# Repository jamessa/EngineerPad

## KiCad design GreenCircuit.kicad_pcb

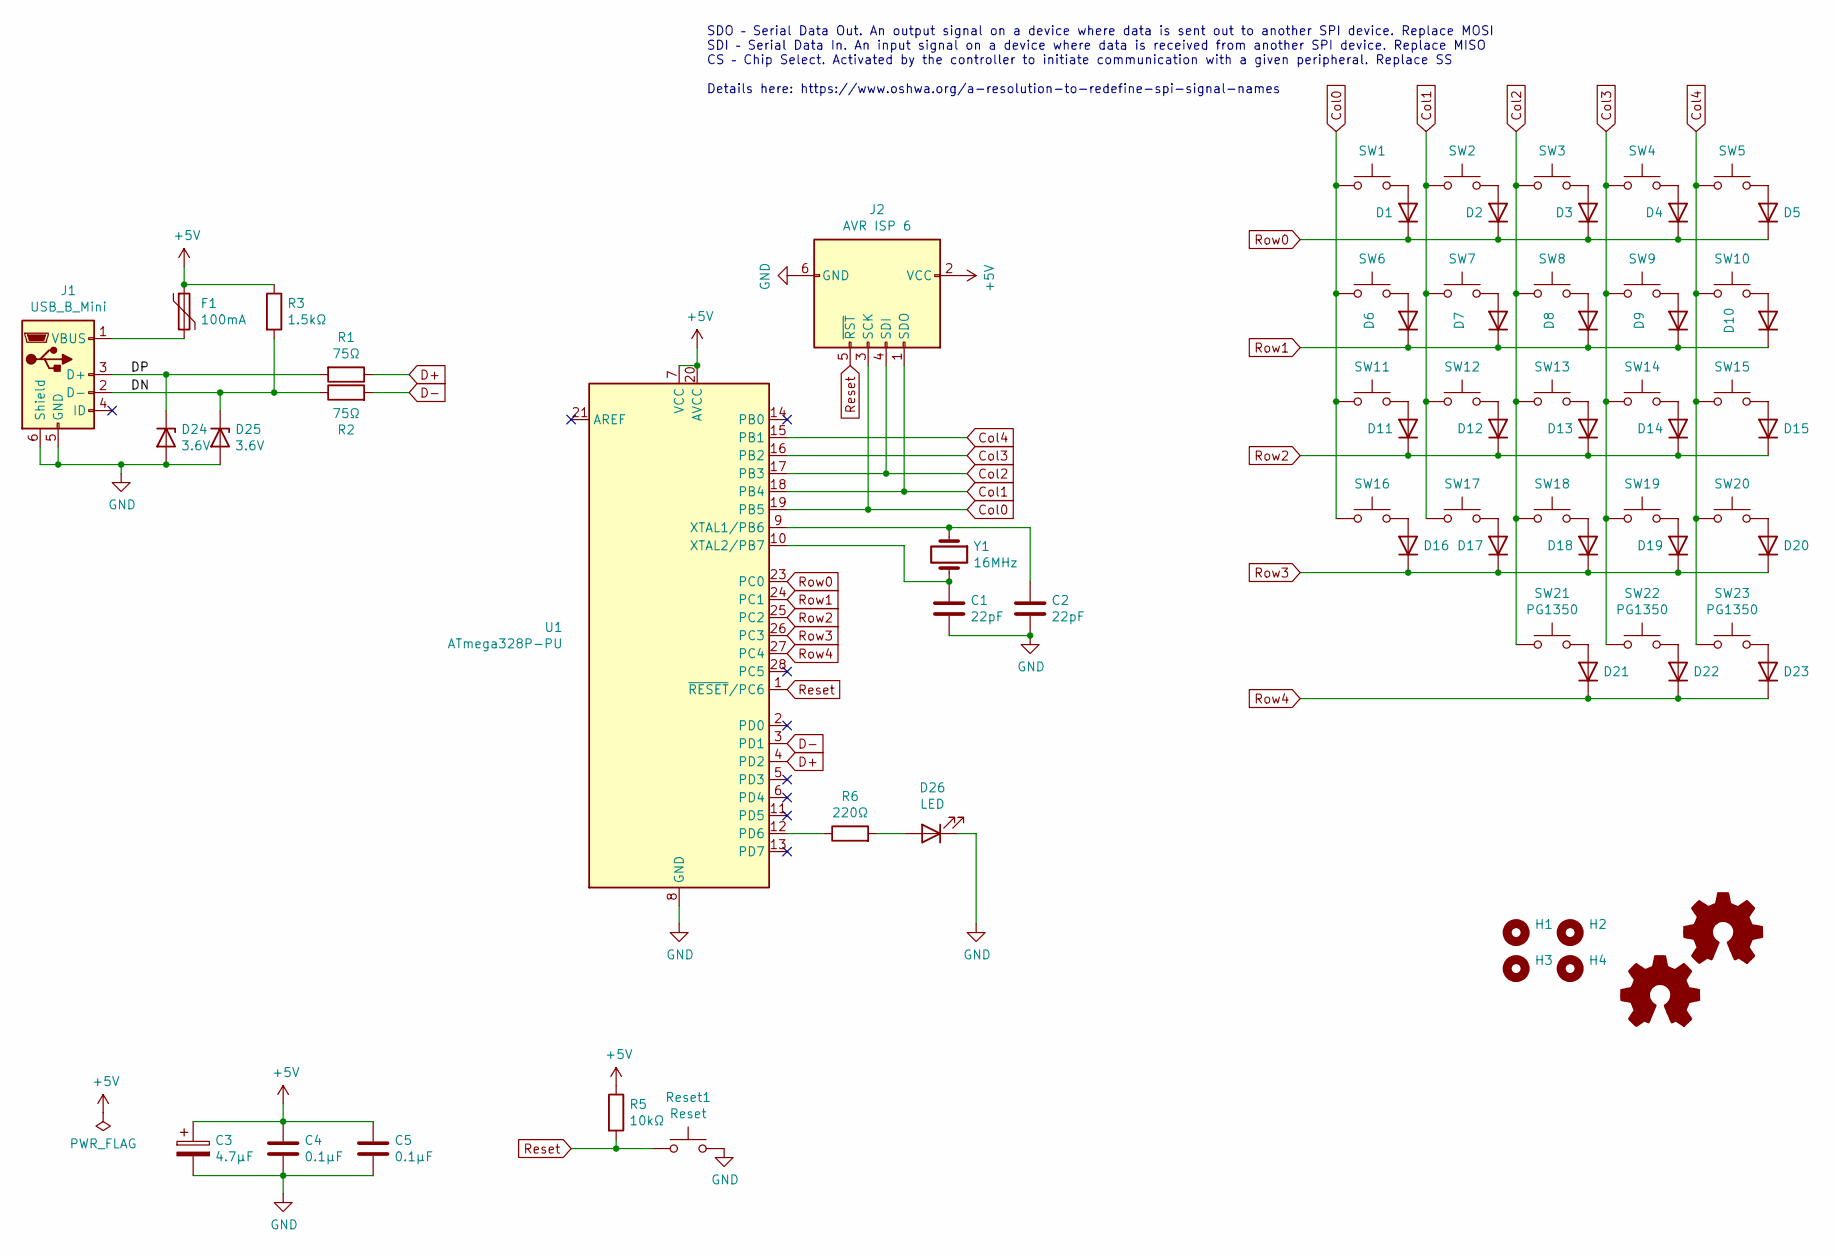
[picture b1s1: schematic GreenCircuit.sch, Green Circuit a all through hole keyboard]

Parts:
C1, C2: 22pF; C_Disc_D3.0mm_W1.6mm_P2.50mm
C3: 4.7μF; CP_Radial_D4.0mm_P1.50mm
C4, C5: 0.1μF; C_Disc_D4.3mm_W1.9mm_P5.00mm
D1, D2, D3, D4, D5, D6, D7, D8, D9, D10, D11, D12, D13, D14, D15, D16, D17, D18, D19, D20, D21, D22, D23: D; Diode_THT
D24, D25: 3.6V; D_DO-35_SOD27_P7.62mm_Horizontal
D26: LED; LED_D3.0mm
F1: 100mA; Fuse_Bourns_MF-RHT050
H1, H2, H3, H4: MountingHole; MountingHole_3.2mm_M3
J1: USB_B_Mini; USB_Mini_B_Female_548190519
J2: AVR ISP 6; AVRISP
R1, R2: 75Ω; R_Axial_DIN0207_L6.3mm_D2.5mm_P7.62mm_Horizontal
R3: 1.5kΩ; R_Axial_DIN0207_L6.3mm_D2.5mm_P7.62mm_Horizontal
R5: 10kΩ; R_Axial_DIN0207_L6.3mm_D2.5mm_P7.62mm_Horizontal
R6: 220Ω; R_Axial_DIN0207_L6.3mm_D2.5mm_P7.62mm_Horizontal
Reset1: Reset; SW_PUSH_6mm
SW1, SW2, SW3, SW4, SW5, SW6, SW7, SW8, SW9, SW10, SW11, SW12, SW13, SW14, SW15, SW16, SW17, SW18, SW19, SW20: SW_Push; SW_Cherry_MX_1.00u_PCB
SW21, SW22, SW23: PG1350; SW_PG1350
U1: ATmega328P-PU; DIP-28_W7.62mm_Socket
Y1: 16MHz; Crystal_HC49-4H_Vertical

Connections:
+5V: C3.1, C4.1, C5.1, F1.1, J2.2 (VCC), R3.1, R5.1, U1.7 (VCC), U1.20 (AVCC)
/DN: D25.1 (K), J1.2 (D-), R2.1, R3.2
/DP: D24.1 (K), J1.3 (D+), R1.2
Col0: J2.3 (SCK), SW1.1, SW6.1, SW11.1, SW16.1, U1.19 (PB5)
Col1: J2.1 (SDO), SW2.1, SW7.1, SW12.1, SW17.1, U1.18 (PB4)
Col2: J2.4 (SDI), SW3.1, SW8.1, SW13.1, SW18.1, SW21.1, U1.17 (PB3)
Col3: SW4.1, SW9.1, SW14.1, SW19.1, SW22.1, U1.16 (PB2)
Col4: SW5.1, SW10.1, SW15.1, SW20.1, SW23.1, U1.15 (PB1)
D+: R1.1, U1.4 (PD2)
D-: R2.2, U1.3 (PD1)
GND: C1.1, C2.1, C3.2, C4.2, C5.2, D24.2 (A), D25.2 (A), D26.1 (K), J1.5 (GND), J1.6 (Shield), J2.6 (GND), Reset1.2, U1.8 (GND), U1.22 (GND)
unnamed: C1.2, U1.10 (XTAL2/PB7), Y1.2
unnamed: C2.2, U1.9 (XTAL1/PB6), Y1.1
unnamed: D1.2 (A), SW1.2
unnamed: D2.2 (A), SW2.2
unnamed: D3.2 (A), SW3.2
unnamed: D4.2 (A), SW4.2
unnamed: D5.2 (A), SW5.2
unnamed: D6.2 (A), SW6.2
unnamed: D7.2 (A), SW7.2
unnamed: D8.2 (A), SW8.2
unnamed: D9.2 (A), SW9.2
unnamed: D10.2 (A), SW10.2
unnamed: D11.2 (A), SW11.2
unnamed: D12.2 (A), SW12.2
unnamed: D13.2 (A), SW13.2
unnamed: D14.2 (A), SW14.2
unnamed: D15.2 (A), SW15.2
unnamed: D16.2 (A), SW16.2
unnamed: D17.2 (A), SW17.2
unnamed: D18.2 (A), SW18.2
unnamed: D19.2 (A), SW19.2
unnamed: D20.2 (A), SW20.2
unnamed: D21.2 (A), SW21.2
unnamed: D22.2 (A), SW22.2
unnamed: D23.2 (A), SW23.2
unnamed: D26.2 (A), R6.2
unnamed: F1.2, J1.1 (VBUS)
unnamed: R6.1, U1.12 (PD6)
Reset: J2.5 (~RST), R5.2, Reset1.1, U1.1 (~RESET~/PC6)
Row0: D1.1 (K), D2.1 (K), D3.1 (K), D4.1 (K), D5.1 (K), U1.23 (PC0)
Row1: D6.1 (K), D7.1 (K), D8.1 (K), D9.1 (K), D10.1 (K), U1.24 (PC1)
Row2: D11.1 (K), D12.1 (K), D13.1 (K), D14.1 (K), D15.1 (K), U1.25 (PC2)
Row3: D16.1 (K), D17.1 (K), D18.1 (K), D19.1 (K), D20.1 (K), U1.26 (PC3)
Row4: D21.1 (K), D22.1 (K), D23.1 (K), U1.27 (PC4)

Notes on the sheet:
SDO – Serial Data Out. An output signal on a device where data is sent out to another SPI device. Replace MOSI SDI – Serial Data In. An input signal on a device where data is received from another SPI device. Replace MISO CS – Chip Select. Activated by the controller to initiate communication with 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

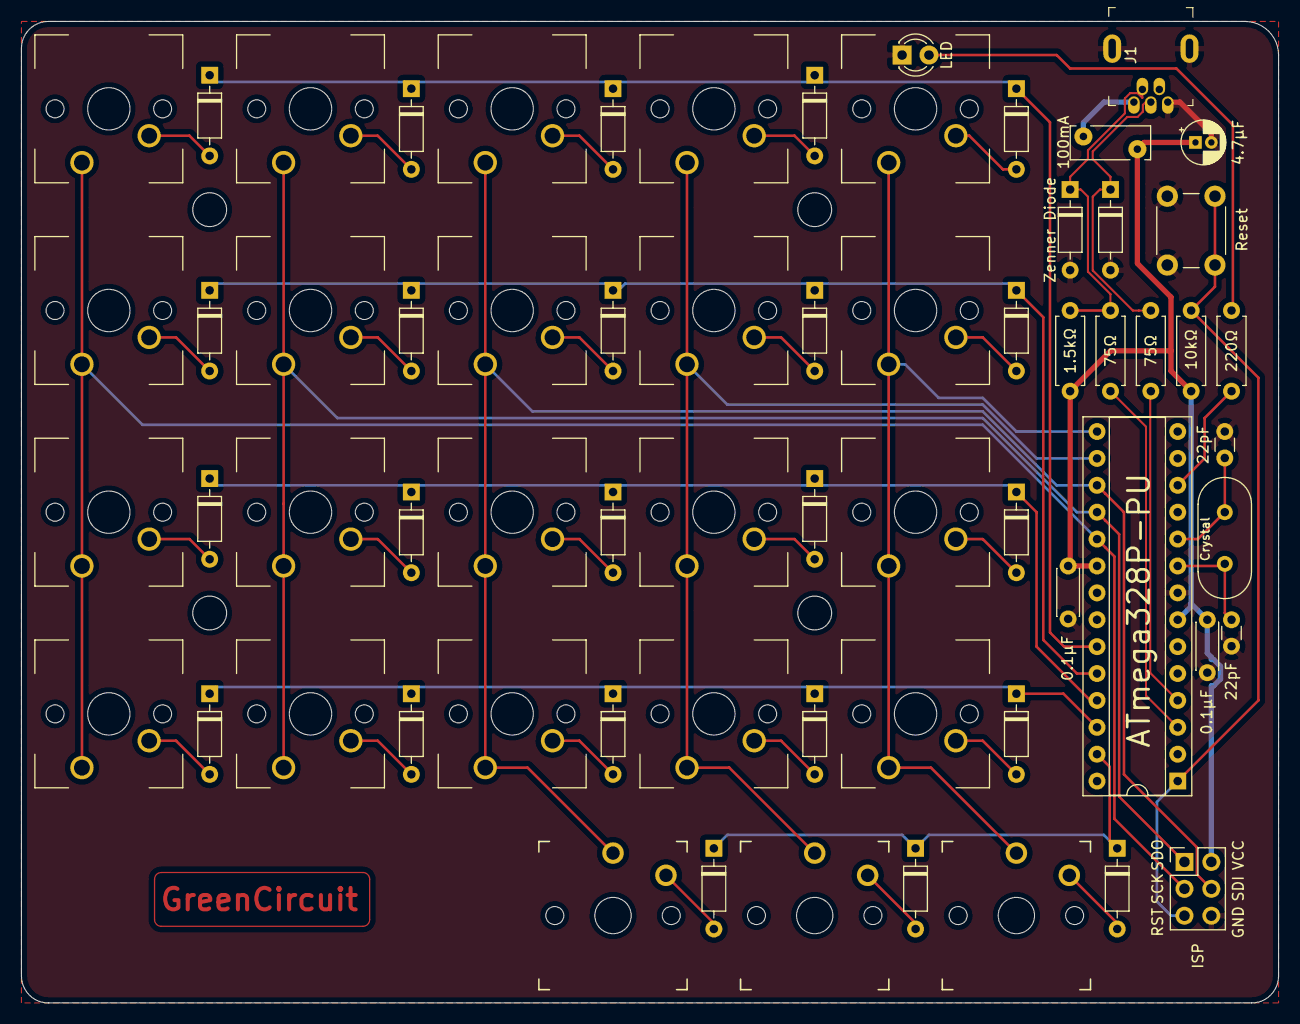
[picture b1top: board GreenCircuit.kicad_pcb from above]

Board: 2 copper layers, 118.7 x 92.7 mm, 69 parts (0 on the bottom side), 45 nets.

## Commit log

2020-08-25 init
2020-08-25 layout change
2020-08-26 remove boot
2020-08-26 switch to type a receptacle
2020-08-26 socket and low profile
2020-08-27 first layout
2020-08-30 Form factor 因為要做成5mm邊框切齊鍵帽，因此PCB從鍵帽處內縮1mm，外殼預計是5mm。
2020-08-31 inch based design
2020-08-31 bump
2020-09-01 handwired
2020-09-01 fix minor wiring
2020-09-01 working version
2020-09-01 silkscreen improvent
2020-09-02 silkscreen and aref to ground
2020-09-02 remove aref add a logo
2020-09-02 export printing file
2020-10-11 Rename and change resistor size
2020-10-11 isp reroute
2020-10-11 add indicative LED
2020-10-12 220ohm for LED
2020-10-13 v0.5
2020-10-25 new pcb size with M3 screw for buttom acrylic
2020-11-02 documents
